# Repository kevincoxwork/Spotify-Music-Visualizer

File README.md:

# Spotify Music Visualizer

MERN Stack application which interacted with Spotify to synchronize music
with LED strips through the Spotify Playback API

Integrated the Spotify Audio Analysis API to perform musical analysis of a
song later visualizing this data on 480 LEDs using a self-developed PCB

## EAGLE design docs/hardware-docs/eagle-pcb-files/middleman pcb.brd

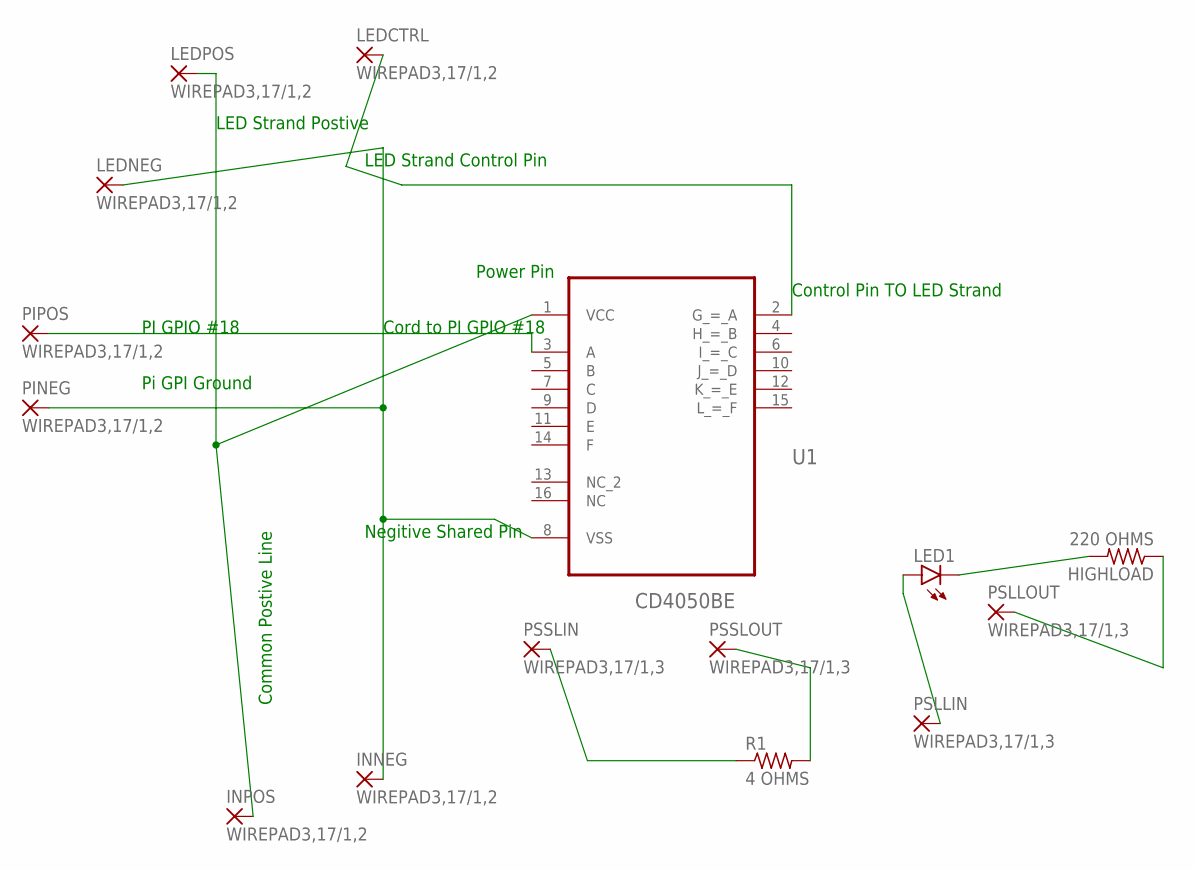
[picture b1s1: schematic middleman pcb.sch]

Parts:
HIGHLOAD: 220 OHMS; R0805
INNEG: WIREPAD3,17/1,2; 3,17/1,2
INPOS: WIREPAD3,17/1,2; 3,17/1,2
LED1: LED3MM
LEDCTRL: WIREPAD3,17/1,2; 3,17/1,2
LEDNEG: WIREPAD3,17/1,2; 3,17/1,2
LEDPOS: WIREPAD3,17/1,2; 3,17/1,2
PINEG: WIREPAD3,17/1,2; 3,17/1,2
PIPOS: WIREPAD3,17/1,2; 3,17/1,2
PSLLIN: WIREPAD3,17/1,3; 3,17/1,3
PSLLOUT: WIREPAD3,17/1,3; 3,17/1,3
PSSLIN: WIREPAD3,17/1,3; 3,17/1,3
PSSLOUT: WIREPAD3,17/1,3; 3,17/1,3
R1: 4 OHMS; R0805
U1: CD4050BE; DIP254P762X508-16

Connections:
unnamed: INPOS.1, LEDPOS.1, U1.1 (VCC)
unnamed: LEDCTRL.1, U1.2 (G_=_A)
unnamed: PIPOS.1, U1.3 (A)
unnamed: LED1.A, PSLLIN.1
unnamed: INNEG.1, LEDNEG.1, PINEG.1, U1.8 (VSS)
unnamed: HIGHLOAD.2, LED1.K (C)
unnamed: HIGHLOAD.1, PSLLOUT.1
unnamed: PSSLIN.1, R1.1
unnamed: PSSLOUT.1, R1.2

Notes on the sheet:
Power Pin
Control Pin TO LED Strand
Cord to PI GPIO #18
Negitive Shared Pin
LED Strand Postive
Common Postive Line
LED Strand Control Pin
Pi GPI Ground
PI GPIO #18

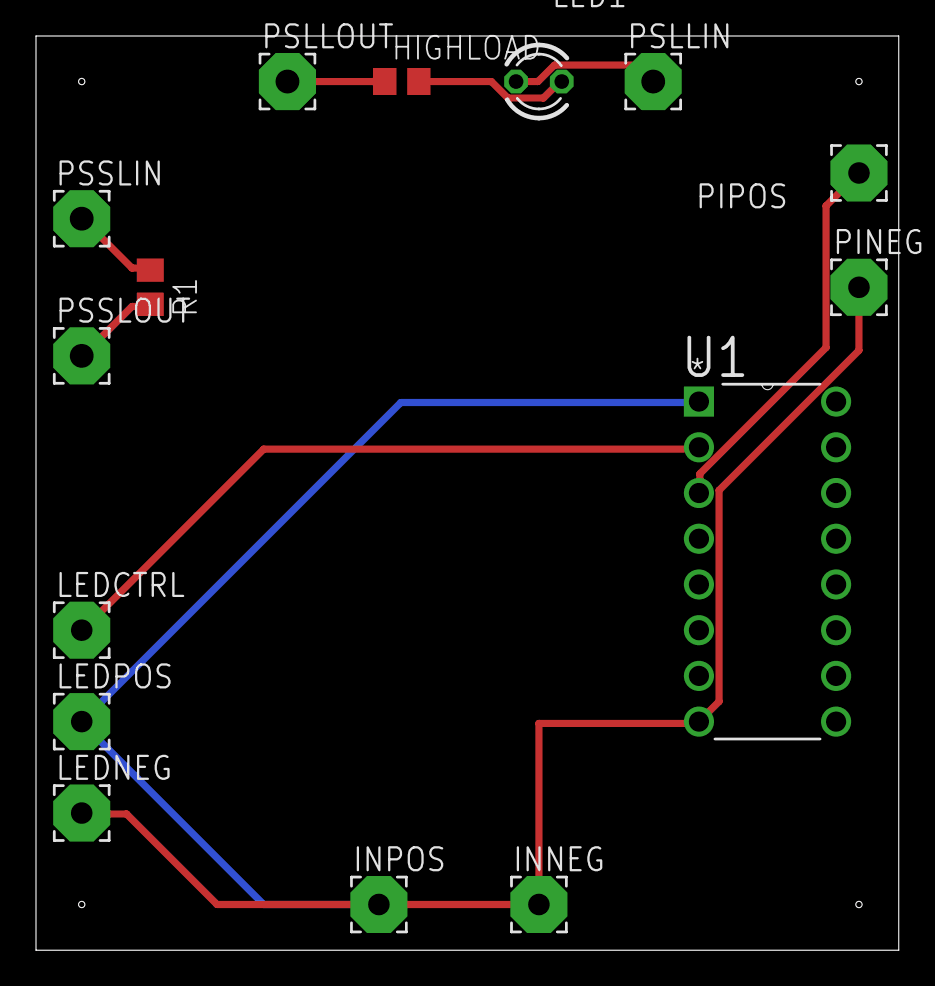
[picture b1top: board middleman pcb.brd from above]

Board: 2 copper layers, 47.9 x 50.8 mm, 15 parts (0 on the bottom side), 9 nets.

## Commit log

2019-09-23 Some hardware docs and formatted readme
2019-09-23 Formatted readme
2019-09-26 Added more details to the hardware docs
2019-09-26 Created workspace
2019-09-26 created env
2019-09-26 moved package.json to root dir
2019-09-26 hello world express
2019-09-26 added call to get api token
2019-09-26 added login authorizaiton for spotify api
2019-09-26 Added basic token get for nomaan
2019-09-26 commiting changes due to merge
2019-09-26 now connects to api and calls can be made with all permissions
2019-09-27 Nomaan Guidance
2019-09-28 Added token request
2019-10-03 Added frontend boilerplate, changed backend structure
2019-10-03 Added rough socket.io visualizer
2019-10-08 added basic login function but no token refresh
2019-10-09 Corrected Logging In. Adding session management later tonight
2019-10-09 Added socket io session and passing data from server->client
2019-10-09 GETs spotify device info from backend and spotify api
2019-10-10 plays song on active device, static song for now will add ability to select later
2019-10-17 Client can retrive playlist data from backend
2019-10-17 Added play/pause/skip l / skip r functionality
2019-10-18 Added landing video
2019-10-18 Quick Fix. Body tag does not apply to all elements
2019-10-19 improved ui with cleaner asthetics and improved font background image for party room still needs to cover whole page without repeating
2019-10-21 Separted the endpoint methods into their own class file. Created a better dynamic device select system
2019-10-23 Added soft visualizer code to run on song playing.
2019-10-27 added scrug buttons for seeking forward and back, back still not working
2019-10-27 removed duplciate invokations of get device status
2019-10-27 seek back is now functioning
2019-10-28 responsiveness improved for desktop and phone use
2019-10-30 Added support for visualization to handle skipping, pausing, replaying, initial playing. Data seems to be lining up
2019-11-04 Added pi light library
2019-11-04 pi urls
2019-11-04 more standard urls
2019-11-04 standard url server side
2019-11-04 forgot to add url export
2019-11-04 server visualization process flow changes
2019-11-04 Completed Visualization. Works correctly and is AWESOME
2019-11-07 Filtered the endpoint return data for the frontend.
2019-11-11 added dynamic scrub bar and fixed css and front end using grids to center content
2019-11-11 removed loop preventing update of current progress on slider
2019-11-11 Correct some issues for nomaan
2019-11-11 Ui changes and more corrections to scrub bar interactions
2019-11-11 album art on smaller devices
2019-11-11 pi font size
2019-11-15 Added playlist choose functionality. Upon clicking playlist it will get playlist tracks. Nomaan to render playlist trakcs
2019-11-24 ensured correct data and params are being passed to play function
2019-11-24 this is to ensure that this ahs the device connected update from select song
2019-11-24 Corrected player changes for nomaan
2019-11-25 correct nomaan's setstate
2019-11-25 cleaned up project errors and fragments
2019-12-06 pi vars for video'
2019-12-06 pi specific change
2021-01-21 Bump socket.io from 2.3.0 to 2.4.0 in /hypeify-server
    Bumps [socket.io](https://github.com/socketio/socket.io) from 2.3.0 to 2.4.0.
    - [Release notes](https://github.com/socketio/socket.io/releases)
    - [Changelog](https://github.com/socketio/socket.io/blob/2.4.0/CHANGELOG.md)
    - [Commits](https://github.com/socketio/socket.io/compare/2.3.0...2.4.0)
2021-05-09 Bump bson from 1.1.1 to 1.1.6 in /hypeify-server
    Bumps [bson](https://github.com/mongodb/js-bson) from 1.1.1 to 1.1.6.
    - [Release notes](https://github.com/mongodb/js-bson/releases)
    - [Changelog](https://github.com/mongodb/js-bson/blob/v1.1.6/HISTORY.md)
    - [Commits](https://github.com/mongodb/js-bson/commits/v1.1.6)
2021-06-30 Bump socket.io-parser from 3.3.0 to 3.3.2 in /hypeify-server
    Bumps [socket.io-parser](https://github.com/socketio/socket.io-parser) from 3.3.0 to 3.3.2.
    - [Release notes](https://github.com/socketio/socket.io-parser/releases)
    - [Changelog](https://github.com/socketio/socket.io-parser/blob/3.3.2/CHANGELOG.md)
    - [Commits](https://github.com/socketio/socket.io-parser/compare/3.3.0...3.3.2)
    ---
    updated-dependencies:
2021-10-04 removed boilerplate readme
2022-02-12 Bump ajv from 6.10.2 to 6.12.6 in /hypeify-server
    Bumps [ajv](https://github.com/ajv-validator/ajv) from 6.10.2 to 6.12.6.
    - [Release notes](https://github.com/ajv-validator/ajv/releases)
    - [Commits](https://github.com/ajv-validator/ajv/compare/v6.10.2...v6.12.6)
    ---
    updated-dependencies:
    - dependency-name: ajv
2022-11-09 Bump socket.io-parser from 3.3.0 to 3.3.3 in /hypeify-server
    Bumps [socket.io-parser](https://github.com/socketio/socket.io-parser) from 3.3.0 to 3.3.3.
    - [Release notes](https://github.com/socketio/socket.io-parser/releases)
    - [Changelog](https://github.com/socketio/socket.io-parser/blob/main/CHANGELOG.md)
    - [Commits](https://github.com/socketio/socket.io-parser/compare/3.3.0...3.3.3)
    ---
    updated-dependencies:
2022-11-23 Bump engine.io and socket.io in /hypeify-server
    Bumps [engine.io](https://github.com/socketio/engine.io) to 3.6.1 and updates ancestor dependency [socket.io](https://github.com/socketio/socket.io). These dependencies need to be updated together.
    Updates `engine.io` from 3.4.0 to 3.6.1
    - [Release notes](https://github.com/socketio/engine.io/releases)
    - [Changelog](https://github.com/socketio/engine.io/blob/main/CHANGELOG.md)
    - [Commits](https://github.com/socketio/engine.io/compare/3.4.0...3.6.1)
    Updates `socket.io` from 2.3.0 to 2.5.0
2022-12-07 Bump qs from 6.5.2 to 6.5.3 in /hypeify-server
    Bumps [qs](https://github.com/ljharb/qs) from 6.5.2 to 6.5.3.
    - [Release notes](https://github.com/ljharb/qs/releases)
    - [Changelog](https://github.com/ljharb/qs/blob/main/CHANGELOG.md)
    - [Commits](https://github.com/ljharb/qs/compare/v6.5.2...v6.5.3)
    ---
    updated-dependencies:
2022-12-11 Bump express from 4.17.1 to 4.17.3 in /hypeify-server
    Bumps [express](https://github.com/expressjs/express) from 4.17.1 to 4.17.3.
    - [Release notes](https://github.com/expressjs/express/releases)
    - [Changelog](https://github.com/expressjs/express/blob/master/History.md)
    - [Commits](https://github.com/expressjs/express/compare/4.17.1...4.17.3)
    ---
    updated-dependencies:
2023-01-24 Bump cookiejar from 2.1.2 to 2.1.4 in /hypeify-server
    Bumps [cookiejar](https://github.com/bmeck/node-cookiejar) from 2.1.2 to 2.1.4.
    - [Release notes](https://github.com/bmeck/node-cookiejar/releases)
    - [Commits](https://github.com/bmeck/node-cookiejar/commits)
    ---
    updated-dependencies:
    - dependency-name: cookiejar
